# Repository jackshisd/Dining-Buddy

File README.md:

# Dining Buddy v6.3  
**ESP32-C3 OLED Keychain for UCLA Dining Menus + Weather Display**

## 🆕 Newest Features 6.0 -> 6.3

-  **Safe Wi-Fi Shutdown:** Device now safely enters deep sleep when unable to connect to Wi-Fi.
-  **Manual Wi-Fi Retry:** Long press the button to retry Wi-Fi connection without rebooting.
-  **Smarter Menu Downloads:** Optimized algorithm avoids redundant downloads, saving time and bandwidth.
-  **Bug Fixes & Stability:** Various minor improvements for a more reliable experience.
-  **Custom Enclosure:** 3D-printed and designed a protective case for portability.
-  **PCB Revision 2:** Updated layout for smoother button presses and improved assembly.

## Overview

Dining Buddy is an ultra-compact ESP32-C3-based keychain device that displays **UCLA dining hall menus** and **real-time weather**, with full offline functionality, minimal power use, and intuitive controls—all on a tiny OLED screen.

Menus are downloaded once daily and displayed with smooth auto-scrolling. The device also includes a **date selection mode**, **hall switching**, and a **live weather page**. It deep sleeps after 30 seconds of inactivity and wakes automatically every night at 2:30 AM to rotate cached menu files and download new ones.

All interaction is handled with a **single button**, and menu data is stored in **SPIFFS**. The PCB was custom-designed in **KiCad** for a minimal, keychain-friendly form factor.

## Photos

### Prototype  

### Finished Keychain 

### Finished Solder Assembly  

### Schematic  

### PCB  

## Features

- 📅 View current and future dining menus (up to 6 days)
- 🏛️ Supports Bruin Plate, Epicuria, De Neve, and Rendezvous
- 🌦️ Weather fetch from [wttr.in](https://wttr.in)
- 🕒 Deep sleep with scheduled nightly wake (2:30 AM)
- 📡 Wi-Fi download over UCLA Wi-Fi or eduroam
- 🪛 Single-button interaction (short, long, double press)
- 🔋 OLED shuts off in deep sleep to preserve battery
- 🧾 All menus saved as clean, compact `.menu` files

## 🔧 Bill of Materials

| Component                    | Description                            |
|-----------------------------|----------------------------------------|
| **ESP32-C3**                | Seeed Studio ESP32-C3 dev board        |
| **OLED Display**            | 0.91" I2C SSD1306 (128×32)             |
| **Push Button**             | 6mm tactile push button                |
| **Custom PCB**              | Designed in KiCad for compact layout   |
| **0603 Resistor** (optional)| 220Ω for LED indicator                 |
| **0603 LED** (optional)     | Miscellaneous LED feedback             |

## 🕹 User Guide

**Navigation is controlled by one button:**

| Press Type        | Action                               |
|------------------|----------------------------------------|
| Short Press       | Next menu section                     |
| Long Press        | Switch to next dining hall            |
| Double Press      | Enter/exit date select mode           |
| Long in Date Mode | Show weather                          |
| Short in Date Mode| Scroll day forward                    |
| Double in Date Mode| Confirm date + return to menu        |
| Inactivity (30s)  | Enter deep sleep                      |

**Modes:**

- **Normal Mode:** Default menu viewing mode with auto-scroll
- **Date Select Mode:** Choose a day (up to 5 days ahead)
- **Weather Mode:** Shows date, time, and latest weather

## How Menus Are Managed

- On first boot, menus for the next 5 days are downloaded.
- Every night at 2:30 AM, yesterday’s menus are deleted, future menus are shifted forward, and the new sixth day is fetched.
- Menu data is extracted from HTML pages and saved as readable text.

## Setup Instructions

1. Flash the ESP32-C3 with the `DiningBuddy` sketch using Arduino IDE.
2. Add your local Wi-Fi or eduroam credentials to `LOCAL_SSID`, `LOCAL_PASS`, and `EAP_*` fields.
3. On boot, the device downloads menus and displays the current one.
4. Power off is automatic after inactivity; just press the button to wake.

## Hardware

- **MCU**: ESP32-C3 (Wi-Fi, deep sleep capable)
- **Display**: 128×32 OLED (SSD1306 via I2C)
- **Button**: Wired to GPIO 2 (input with pull-up)
- **LED**: Optional, wired to GPIO 21 via 220Ω resistor
- **Power**: LiPo or USB 5V
- **PCB**: Designed in KiCad for ultra-compact fit on a keychain

## Future Improvements

- Battery charging circuit on PCB  
- Auto time zone detection via Wi-Fi  
- Menu item filtering (vegetarian, vegan, etc.)  
- BLE companion app?

## 👤 Author

**Jack Shi**  
📧 jackmshi@ucla.edu  
🔬 UCLA Electrical Engineering

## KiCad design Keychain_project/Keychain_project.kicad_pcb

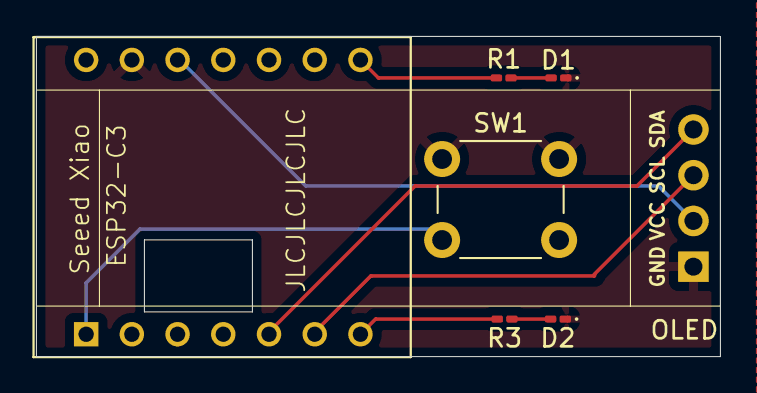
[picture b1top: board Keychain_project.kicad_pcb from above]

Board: 2 copper layers, 38.0 x 17.8 mm, 7 parts (0 on the bottom side), 10 nets.

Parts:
D1, D2: LED; LED_0201_0603Metric_Pad0.64x0.40mm_HandSolder
R1, R3: 220; R_0201_0603Metric_Pad0.64x0.40mm_HandSolder
SW1: SW_Push; SW_PUSH_6mm
U1: ESP32-C3; MODULE_113991054
U2: SSD1306-0.91-OLED-4pin-128x32 (REVERSED)

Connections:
+3.3V: U1.12 (MTCK), U2.2 (SCL)
GND: D1.1 (K), D2.1 (K), SW1.1, U1.13 (MTDO), U2.1 (SDA)
unnamed: D1.2 (A), R1.2
unnamed: D2.2 (A), R3.1
unnamed: R3.2, U1.7 (CHIP_EN)
unnamed: U1.6 (GPIO2), U2.3 (VCC)
unnamed: R1.1, U1.8 (GPIO3)
unnamed: SW1.2, U1.1 (LNA_IN)
unnamed: U1.2 (VDD3P3), U1.3 (VDD3P3)
unnamed: U1.5 (XTAL_32K_N), U2.4 (GND)

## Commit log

2025-07-22 added code, gerbers, and photos
2025-07-22 added files of assembly
2025-07-25 Upload Kicad Files
2025-08-01 Create text
2025-08-01 Rename pcb2.png to pictures/pcb2.png
2025-08-01 Rename pcb1.png to pictures/pcb1.png
2025-08-01 Rename prototype.png to pictures/prototype.png
2025-08-01 Rename back.png to pictures/back.png
2025-08-01 Rename front.png to pictures/front.png
2025-08-01 Rename schematic.png to picutres/schematic.png
2025-08-01 Rename side.png to pictures/side.png
2025-08-01 Fixed photos and deleted unnecessary files
2025-08-01 added 3d print files
